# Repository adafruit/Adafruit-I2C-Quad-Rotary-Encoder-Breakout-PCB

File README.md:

## Adafruit I2C Quad Rotary Encoder Breakout with NeoPixel - STEMMA QT / Qwiic PCB

<a href="http://www.adafruit.com/products/5752"><br/>
Click here to purchase one from the Adafruit shop</a>

PCB files for the Adafruit I2C Quad Rotary Encoder Breakout with NeoPixel - STEMMA QT / Qwiic. 

Format is EagleCAD schematic and board layout
* https://www.adafruit.com/product/5752

### Description

Rotary encoders are soooo much fun! Twist em this way, then twist them that way. Unlike potentiometers, they go all the way around and often have little detents for tactile feedback. But, if you've ever tried to add encoders to your project you know that they're a real challenge to use: timers, interrupts, debouncing...

This Stemma QT breakout makes all that frustration go away - and allows you to read up to 4 encoders for big builds with lots of twisty interfaces. You can solder in any four 'standard' PEC11-pinout rotary encoders with or without a push-switch. The onboard microcontroller is programmed with our seesaw firmware and will track all pulses and pins for you and then save the incremental value for querying at any time over I2C. Plug it in with a Stemma QT cable for instant rotary goodness, with any kind of microcontroller from an Arduino UNO up to a Raspberry Pi.

You can use our Arduino library to control and read data with any compatible microcontroller. We also have CircuitPython/Python code for use with computers or single-board Linux boards.

It's also easy to add this breakout to a breadboard - with six 0.1"-spaced breakout pads. Power with 3 to 5V DC and then use 3 or 5V logic I2C data. The INT pin can be configured to pulse low whenever rotation or push-buttoning is detected so you do not have to spam-read the I2C port to detect motion.

If you happen to be using clear/translucent shaft encoders, there are reverse-mount NeoPixels on board, that can display any color you like, they are controlled over I2C for additional visual feedback or keep them off if you like. Note that for metal-shaft encoders, the LEDs are not visible. On the back, there's a green power LED as well as a red INT LED that, if the interrupt is configured, will blink when the interrupt fires.

Using the three onboard address jumpers, you can connect up to 8 of these encoders on a single I2C port. The first one will be at address 0x49, the last one at 0x51 when all three jumpers are cut open.

To get you going fast, we spun up a custom-made PCB with the seesaw chip and all supporting circuitry, in the STEMMA QT form factor, making them easy to interface with. The STEMMA QT connectors on either side are compatible with the SparkFun Qwiic I2C connectors. This allows you to make solderless connections between your development board and the rotary encoder or to chain them with a wide range of other sensors and accessories using a compatible cable. QT Cable is not included, but we have a variety in the shop.

This breakout does not come with any encoders soldered on, so you can pick whatever encoder you like. We sell a common 24-detent-with-switch encoder here and it works wonderfully. You can also use encoders without detents or with a different number of detents per rotation, of course! You'll need to solder the encoders and optional header onto the PCB to use with a solderless breadboard. but it's fairly easy and takes only a few minutes even for a beginner.

### License

Adafruit invests time and resources providing this open source design, please support Adafruit and open-source hardware by purchasing products from [Adafruit](https://www.adafruit.com)!

Designed by Limor Fried/Ladyada for Adafruit Industries.

Creative Commons Attribution/Share-Alike, all text above must be included in any redistribution. 
See license.txt for additional details.

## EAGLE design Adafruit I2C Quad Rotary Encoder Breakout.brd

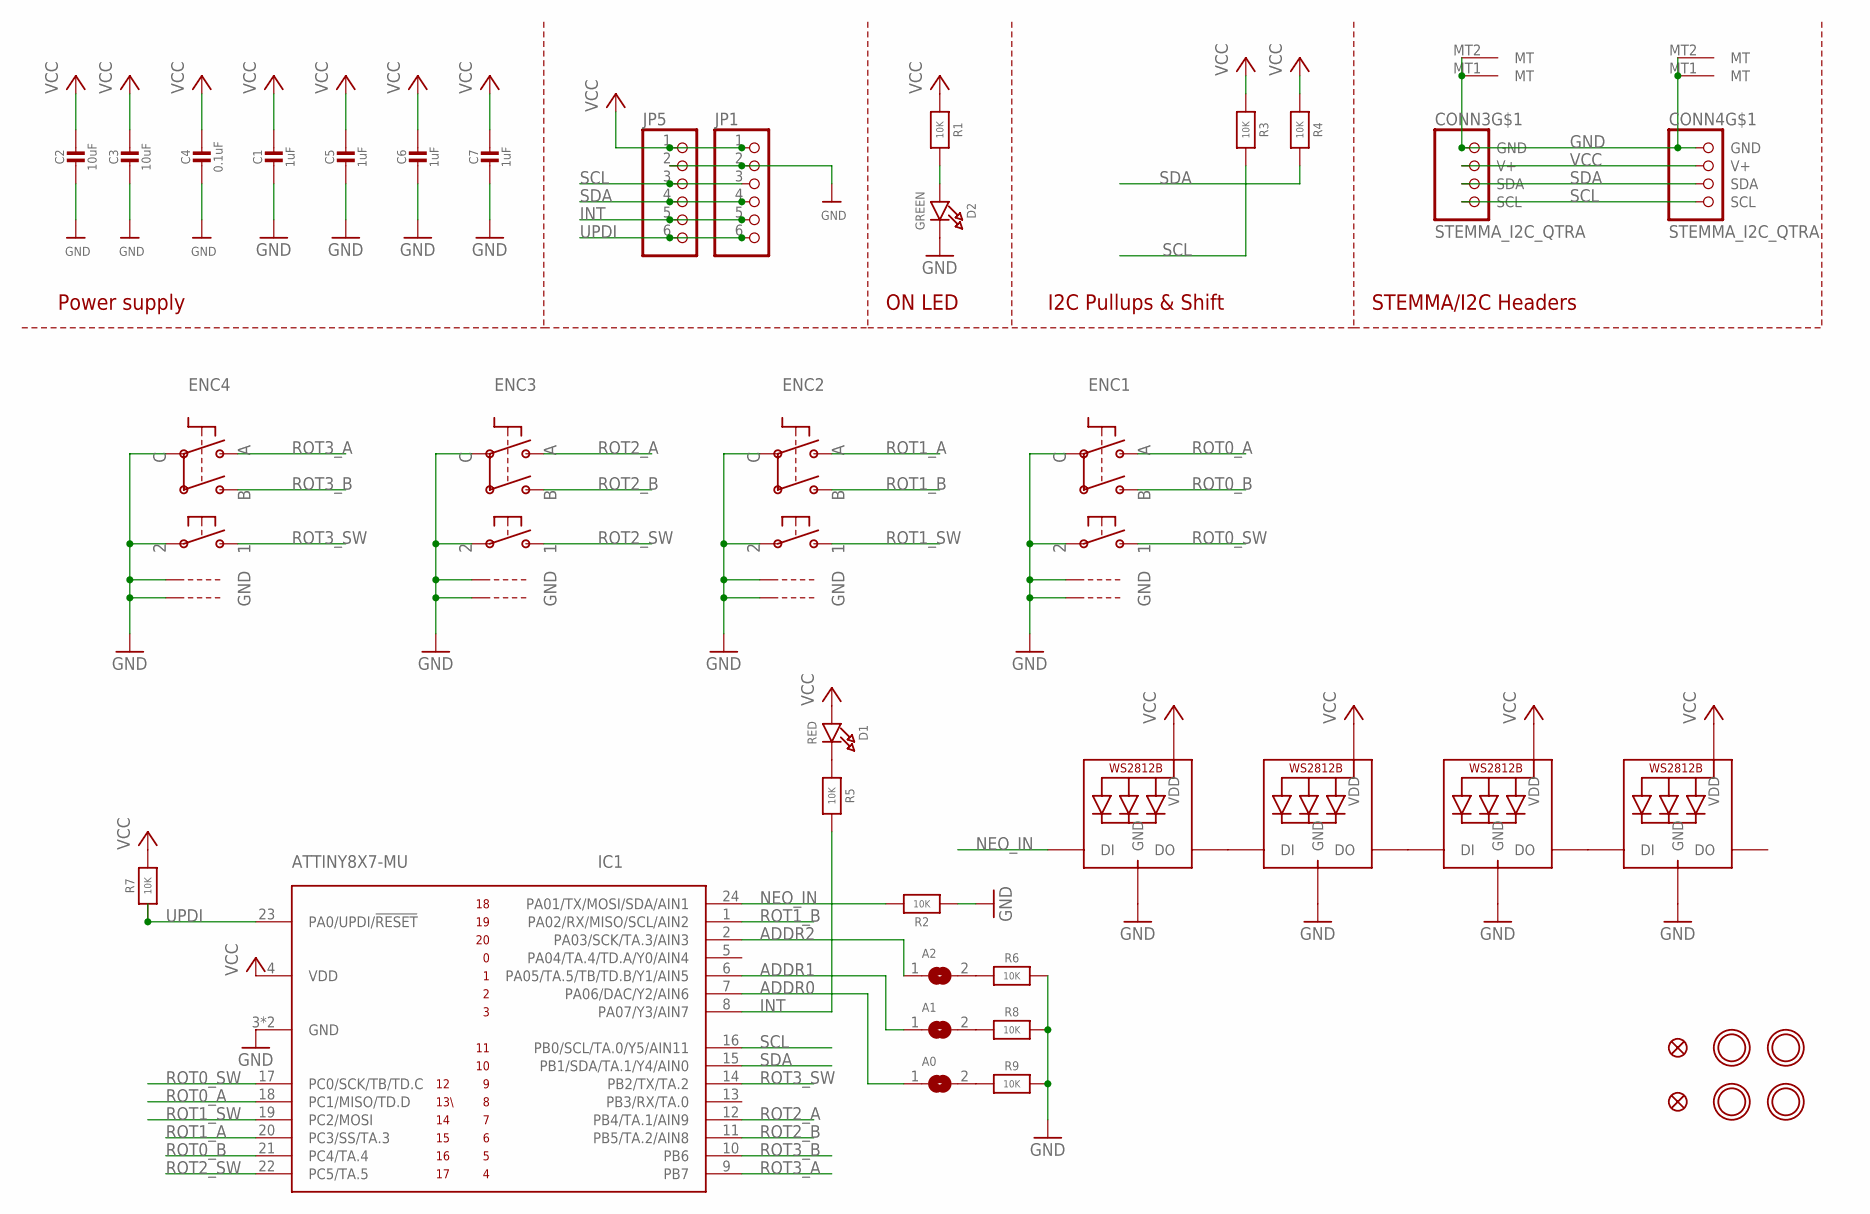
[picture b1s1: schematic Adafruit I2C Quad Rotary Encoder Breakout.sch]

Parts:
A0, A1, A2: SOLDERJUMPERCLOSED; SOLDERJUMPER_CLOSEDWIRE
C1, C5, C6, C7: 1uF; 0603-NO
C2, C3: 10uF; 0805-NO
C4: 0.1uF; 0603-NO
CONN3, CONN4: STEMMA_I2C_QTRA; JST_SH4_RA
D1: RED; CHIPLED_0603_NOOUTLINE
D2: GREEN; CHIPLED_0603_NOOUTLINE
ENC1, ENC2, ENC3, ENC4: ENCODER_PLUS_SWITCH_BOURNS_PEC11; PEC11+SWITCH
FID1, FID2: FIDUCIAL_1MM
IC1: ATTINY8X7-MU; QFN24_4MM
JP1, JP5: HEADER-1X670MIL; 1X06_ROUND_70
LED1, LED2, LED3, LED4: WS2812B_SK6812E; NEO3535_REVERSE
R1, R2, R3, R4, R5, R6, R7, R8, R9: 10K; 0603-NO
U$3, U$17, U$19, U$21: MOUNTINGHOLE2.5; MOUNTINGHOLE_2.5_PLATED

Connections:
ADDR0: A0.1, IC1.7 (PA06/DAC/Y2/AIN6)
ADDR1: A1.1, IC1.6 (PA05/TA.5/TB/TD.B/Y1/AIN5)
ADDR2: A2.1, IC1.2 (PA03/SCK/TA.3/AIN3)
GND: C1.2, C2.2, C3.2, C4.2, C5.2, C6.2, C7.2, CONN3.1 (GND), CONN3.MT1 (MT), CONN3.MT2 (MT), CONN4.1 (GND), CONN4.MT1 (MT), CONN4.MT2 (MT), D2.C, ENC1.P$2, ENC1.P$C, ENC1.P$GND1, ENC1.P$GND2, ENC2.P$2, ENC2.P$C, ENC2.P$GND1, ENC2.P$GND2, ENC3.P$2, ENC3.P$C, ENC3.P$GND1, ENC3.P$GND2, ENC4.P$2, ENC4.P$C, ENC4.P$GND1, ENC4.P$GND2, IC1.3 (GND), IC1.THERM (GND), JP1.2, JP5.2, LED1.3-GND (GND), LED2.3-GND (GND), LED3.3-GND (GND), LED4.3-GND (GND), R2.1, R6.2, R8.2, R9.2
INT: IC1.8 (PA07/Y3/AIN7), JP1.5, JP5.5, R5.2
unnamed: D2.A, R1.2
unnamed: LED1.2-DOUT (DO), LED2.4-DIN (DI)
unnamed: LED2.2-DOUT (DO), LED3.4-DIN (DI)
unnamed: LED3.2-DOUT (DO), LED4.4-DIN (DI)
unnamed: D1.C, R5.1
unnamed: A2.2, R6.1
unnamed: A1.2, R8.1
unnamed: A0.2, R9.1
NEO_IN: IC1.24 (PA01/TX/MOSI/SDA/AIN1), LED1.4-DIN (DI), R2.2
ROT0_A: ENC1.P$A, IC1.18 (PC1/MISO/TD.D)
ROT0_B: ENC1.P$B, IC1.21 (PC4/TA.4)
ROT0_SW: ENC1.P$1, IC1.17 (PC0/SCK/TB/TD.C)
ROT1_A: ENC2.P$A, IC1.20 (PC3/SS/TA.3)
ROT1_B: ENC2.P$B, IC1.1 (PA02/RX/MISO/SCL/AIN2)
ROT1_SW: ENC2.P$1, IC1.19 (PC2/MOSI)
ROT2_A: ENC3.P$A, IC1.12 (PB4/TA.1/AIN9)
ROT2_B: ENC3.P$B, IC1.11 (PB5/TA.2/AIN8)
ROT2_SW: ENC3.P$1, IC1.22 (PC5/TA.5)
ROT3_A: ENC4.P$A, IC1.9 (PB7)
ROT3_B: ENC4.P$B, IC1.10 (PB6)
ROT3_SW: ENC4.P$1, IC1.14 (PB2/TX/TA.2)
SCL: CONN3.4 (SCL), CONN4.4 (SCL), IC1.16 (PB0/SCL/TA.0/Y5/AIN11), JP1.3, JP5.3, R3.2
SDA: CONN3.3 (SDA), CONN4.3 (SDA), IC1.15 (PB1/SDA/TA.1/Y4/AIN0), JP1.4, JP5.4, R4.2
UPDI: IC1.23 (PA0/UPDI/!RESET), JP1.6, JP5.6, R7.1
VCC: C1.1, C2.1, C3.1, C4.1, C5.1, C6.1, C7.1, CONN3.2 (V+), CONN4.2 (V+), D1.A, IC1.4 (VDD), JP1.1, JP5.1, LED1.1-VDD (VDD), LED2.1-VDD (VDD), LED3.1-VDD (VDD), LED4.1-VDD (VDD), R1.1, R3.1, R4.1, R7.2

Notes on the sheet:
I2C Pullups & Shift
STEMMA/I2C Headers
ON LED
Power supply

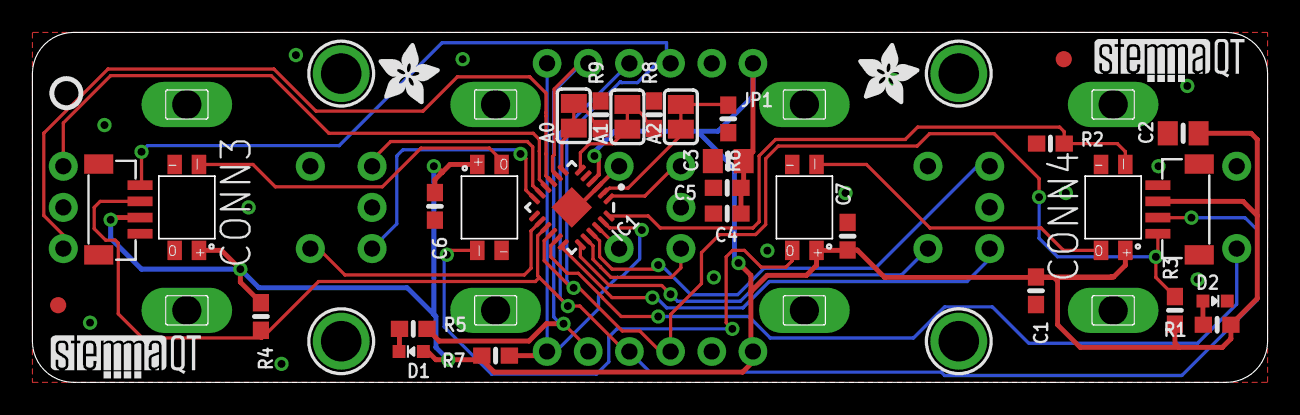
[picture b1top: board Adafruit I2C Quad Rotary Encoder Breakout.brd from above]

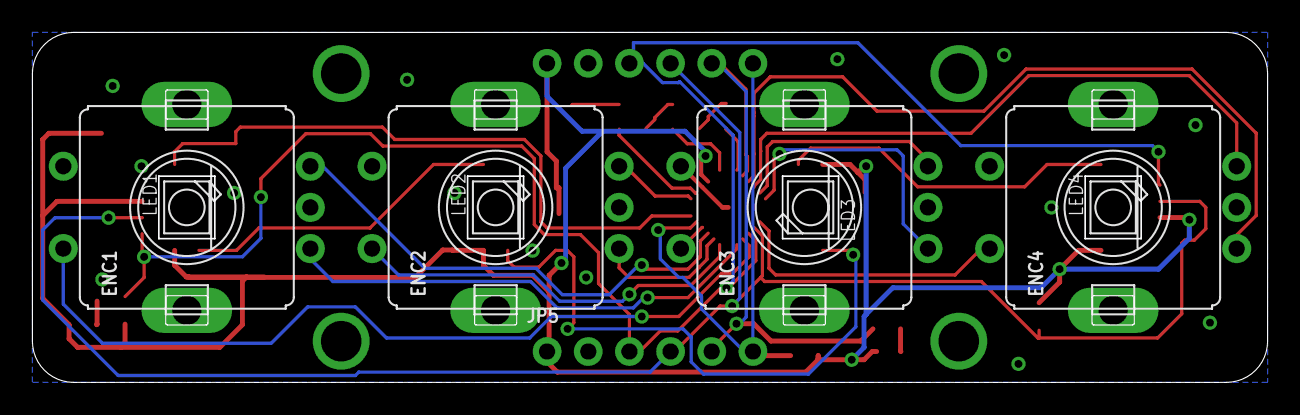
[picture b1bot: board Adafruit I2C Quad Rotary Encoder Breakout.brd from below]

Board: 2 copper layers, 76.2 x 21.6 mm, 78 parts (25 on the bottom side), 30 nets.

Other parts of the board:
PLABEL0: PLABEL0
PLABEL1: PLABEL1
PLABEL2: PLABEL2
PLABEL3: PLABEL3
PLABEL4: PLABEL4
PLABEL5: PLABEL5
PLABEL6: PLABEL6
PLABEL7: PLABEL7
PLABEL8: PLABEL8
PLABEL9: PLABEL9
PLABEL10: PLABEL10
PLABEL11: PLABEL11
PLABEL12: PLABEL12
PLABEL13: PLABEL13
PLABEL14: PLABEL14
PLABEL15: PLABEL15
PLABEL16: PLABEL16
PLABEL17: PLABEL17
PLABEL18: PLABEL18
PLABEL19: PLABEL19
PLABEL20: PLABEL20
PLABEL21: PLABEL21
PLABEL22: PLABEL22
PLABEL23: PLABEL23
PLABEL24: PLABEL24
PLABEL25: PLABEL25
PLABEL26: PLABEL26
PLABEL27: PLABEL27
PLABEL28: PLABEL28
PLABEL29: PLABEL29
PLABEL30: PLABEL30
PLABEL31: PLABEL31
PLABEL32: PLABEL32
U$2, U$9: ADAFRUIT_3.5MM
U$25: PCBFEAT-REV-040
U$30, U$31: STEMMAQT

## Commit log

2023-06-30 adding cookiecutter output

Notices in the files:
parts and their libraries:
microbuilder: This work is placed in the public domain, and may be freely used for commercial and non-commercial work with the following conditions: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
